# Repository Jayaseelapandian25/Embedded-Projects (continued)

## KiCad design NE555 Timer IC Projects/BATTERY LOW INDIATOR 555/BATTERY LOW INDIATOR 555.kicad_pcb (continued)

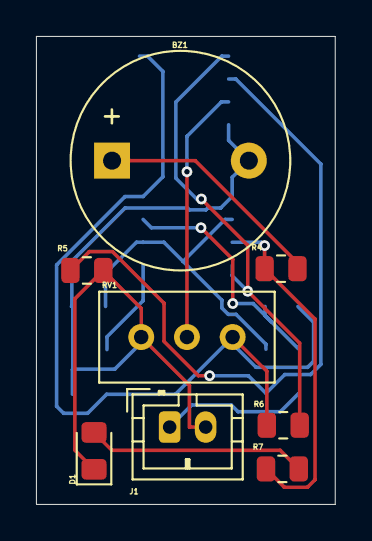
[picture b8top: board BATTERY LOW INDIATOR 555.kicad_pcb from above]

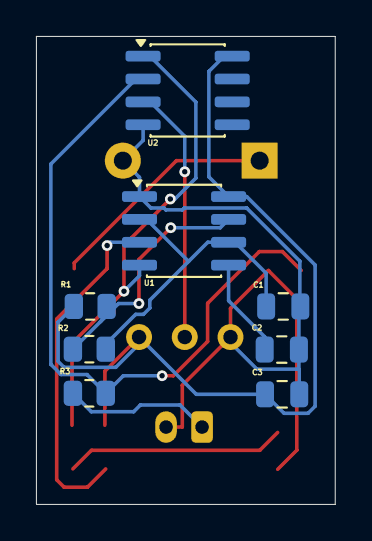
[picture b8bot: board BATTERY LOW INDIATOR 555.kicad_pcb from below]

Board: 2 copper layers, 16.6 x 26.0 mm, 16 parts (8 on the bottom side), 12 nets.
